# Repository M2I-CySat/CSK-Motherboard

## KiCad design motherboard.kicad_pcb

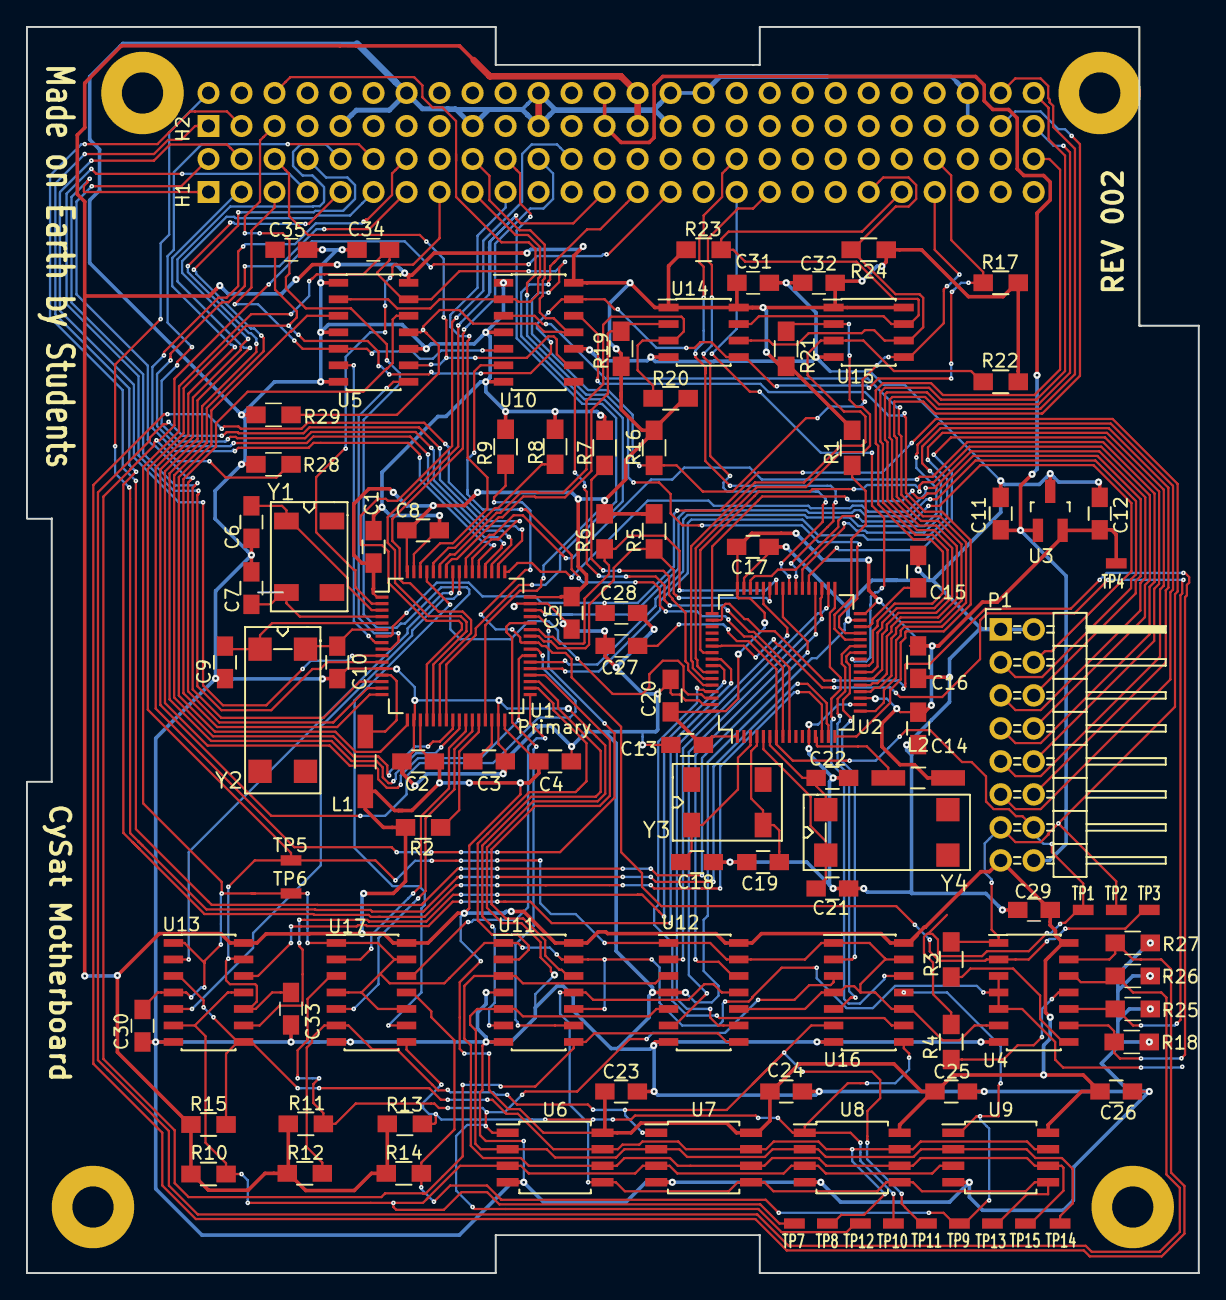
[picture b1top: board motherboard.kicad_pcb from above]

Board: 2 copper layers, 90.2 x 95.9 mm, 106 parts (1 on the bottom side), 123 nets.

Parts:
C1, C11, C12, C13, C27, C28: 1uF; C_0805_HandSoldering
C2, C4, C5, C8, C14, C16, C17, C20, C23, C24, C25, C26, C29, C30, C31, C32, C33, C34, C35: 0.1uF; C_0805_HandSoldering
C3, C15: 4.7uF; C_0805_HandSoldering
C6, C7, C18, C19: 4.3pF; C_0805_HandSoldering
C9, C10, C21, C22: 20pF; C_0805_HandSoldering
H1, H2: CONN_02X26; CSK_Header
L1, L2: BEAD; Choke_SMD_1206_Handsoldering
LOGO: LOGO
P1: CONN_02X08; Pin_Header_Angled_2x08
R1, R2, R3, R4, R5, R6, R7, R8, R9, R10, R11, R12, R13, R14, R15, R16, R17, R18, R25, R26, R27, R28, R29: 100K; R_0805_HandSoldering
R19, R20, R21, R22, R23, R24: 4.7K; R_0805_HandSoldering
TP1, TP2, TP3, TP4, TP5, TP6, TP7, TP8, TP9, TP10, TP11, TP12, TP13, TP14, TP15: TP; TP_0603
U1, U2: STM32F411-LQFP64; LQFP-64_10x10mm_Pitch0.5mm
U3: AP7313; SOT-23_Handsoldering
U4: 74LS00; SOIC-14_3.9x8.7mm_Pitch1.27mm
U5, U10, U11, U12, U13, U16, U17: 74LS125; SOIC-14_3.9x8.7mm_Pitch1.27mm
U6, U7, U8, U9: FM25V20A-G; SOIJ-8_5.3x5.3mm_Pitch1.27mm
U14, U15: PCA9517A; SOIC-8_3.9x4.9mm_Pitch1.27mm
Y1, Y3: 32k; SOJ-4_5.5mm
Y2, Y4: 8M(16pF); SOJ-4_9.4mm

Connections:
+3V3: C1.2, C2.2, C4.2, C5.2, C8.2, C23.2, C24.2, C25.2, C26.2, C29.1, C31.1, C32.1, H2.27, H2.28, L1.2, P1.15, R1.2, R2.2, R5.2, R6.2, R10.1, R11.1, R12.1, R13.1, R14.1, R15.1, R16.2, R17.2, R19.2, R20.2, R21.2, R22.2, R23.1, R24.1, U1.1, U1.19, U1.32, U1.48, U1.64, U4.14, U5.14, U6.8, U7.8, U8.8, U9.8, U10.14, U11.14, U12.14, U13.14, U14.1, U14.8, U15.1, U15.8, U16.14, U17.14
+5V: C11.1, H2.25, H2.26, P1.16, U3.1
/BOOT0_P: R8.1, U1.60
/BOOT0_S: R7.1, U2.60
/BOOT1_P: R2.1, U1.28
/BOOT1_S: R1.1, U2.28
/GPIO0: H1.1, U1.14
/GPIO1: H1.2, U1.15
/GPIO2: H1.3, U1.45
/GPIO3: H1.4, U1.10
/GPIO4: H1.7, U1.11
/GPIO5: H1.8, U1.24
/GPIO6: H1.9, U1.25
/GPIO7: H1.10, U1.39
/GPIO8: H1.11, U1.40
/GPIO9: H1.12, U1.51
/GPIO10: H1.13, U1.52
/GPIO11: H1.14, U1.53
/GPIO12: H1.15, U1.2
/I2C2_SCL: H1.20, U1.29
/I2C2_SDA: H1.19, U1.62
/I2C3_SCL: H2.6, U2.29
/I2C3_SDA: H2.5, U2.62
/MEM_CS0: R14.2, TP9.1, U9.1, U16.11, U17.11
/MEM_CS0_P: U1.33, U17.12
/MEM_CS0_S: U2.33, U16.12
/MEM_CS1: R13.2, TP10.1, U8.1, U16.8, U17.8
/MEM_CS1_P: U1.61, U17.9
/MEM_CS1_S: U2.61, U16.9
/MEM_CS2: R12.2, TP11.1, U7.1, U16.6, U17.6
/MEM_CS2_P: U1.27, U17.5
/MEM_CS2_S: U2.27, U16.5
/MEM_CS3: R11.2, TP12.1, U6.1, U16.3, U17.3
/MEM_CS3_P: U1.26, U17.2
/MEM_CS3_S: U2.26, U16.2
/MEM_MISO: TP14.1, U6.2, U7.2, U8.2, U9.2, U11.5, U12.5
/MEM_MISO_P: U1.35, U11.6
/MEM_MISO_S: U2.35, U12.6
/MEM_MOSI: TP13.1, U6.5, U7.5, U8.5, U9.5, U11.11, U12.11
/MEM_MOSI_P: U1.36, U11.12
/MEM_MOSI_S: U2.36, U12.12
/MEM_NHOLD: R15.2, TP8.1, U6.7, U7.7, U8.7, U9.7, U13.3, U13.8
/MEM_NHOLD_P: U1.57, U13.2
/MEM_NHOLD_S: U2.57, U13.9
/MEM_NWP: R10.2, TP7.1, U6.3, U7.3, U8.3, U9.3, U13.6, U13.11
/MEM_NWP_P: U1.56, U13.5
/MEM_NWP_S: U2.56, U13.12
/MEM_SCK: TP15.1, U6.6, U7.6, U8.6, U9.6, U11.3, U12.3
/MEM_SCK_P: U1.34, U11.2
/MEM_SCK_S: U2.34, U12.2
/NBUFEN_PRI: C30.1, C34.1, H1.45, R16.1, TP6.1, U4.3, U4.4, U4.5, U5.13, U11.1, U11.10, U11.13, U13.1, U13.4, U15.5, U17.1, U17.4, U17.10, U17.13
/NBUFEN_SEC: C33.1, C35.1, H1.46, R17.1, TP5.1, U4.6, U10.13, U12.1, U12.10, U12.13, U13.10, U13.13, U14.5, U16.1, U16.4, U16.10, U16.13
/NRST_P: C27.2, P1.13, R3.2, TP2.1, U1.7, U4.1
/NRST_S: C28.2, P1.14, R4.2, TP1.1, U2.7
/NYIELD_P: R9.1, TP3.1, U1.41, U4.2
/PRX_STX: R6.1, U1.43, U2.42
/PTX_SRX: R5.1, U1.42, U2.43
/RADIO_RR: H1.6, U5.9, U10.9
/RADIO_RR_P: U1.9, U5.8
/RADIO_RR_S: U2.9, U10.8
/RADIO_RX: H1.17, U5.2, U10.2
/RADIO_RX_P: U1.17, U5.3
/RADIO_RX_S: U2.17, U10.3
/RADIO_TR: H1.5, U5.5, U10.5
/RADIO_TR_P: U1.8, U5.6
/RADIO_TR_S: U2.8, U10.6
/RADIO_TX: H1.18, R29.2, U5.11, U10.11
/RADIO_TX_P: U1.16, U5.12
/RADIO_TX_S: U2.16, U10.12
/RST1_P: R18.1, U2.50, U4.9
/RST1_S: R26.1, U1.50, U4.12
/RST2_P: R25.1, U2.54, U4.10
/RST2_S: R27.1, U1.54, U4.13
/SGPIO0: H2.1, U2.14
/SGPIO1: H2.2, U2.15
/SGPIO2: H2.3, U2.41
/SGPIO6: H1.52, U2.24
/SGPIO7: H1.33, U2.25
/SGPIO8: H1.34, U2.39
/SGPIO9: H1.35, U2.40
/SPI2_MISO: H2.51, U2.22
/SPI2_MOSI: H2.52, U2.23
/SPI2_NSS: H2.49, U2.20
/SPI2_SCK: H2.50, U2.21
/SWO_P: P1.7, U1.55
/SWO_S: P1.8, U2.55
/SYS_RESET: H1.29, R28.2, U11.8, U12.8
/SYS_RESET_P: U1.44, U11.9
/SYS_RESET_S: U2.44, U12.9
/SYS_SCL: H1.43, R23.2, U14.7, U15.7
/SYS_SCL_P: R19.1, U1.58, U14.2
/SYS_SCL_S: R21.1, U2.58, U15.2
/SYS_SDA: H1.41, R24.2, U14.6, U15.6
/SYS_SDA_P: R20.1, U1.59, U14.3
/SYS_SDA_S: R22.1, U2.59, U15.3
/SYS_SPI_MISO: H1.22, U1.22
/SYS_SPI_MOSI: H1.27, U1.23
/SYS_SPI_NSS: H1.24, U1.20
/SYS_SPI_SCK: H1.25, U1.21
/TCK_P: P1.5, U1.49
/TCK_S: P1.6, U2.49
/TMS_P: P1.3, U1.46
/TMS_S: P1.4, U2.46
/UART2_RX: P1.11, U1.38
/UART2_TX: P1.9, U1.37
/UART3_RX: P1.12, U2.38
/UART3_TX: P1.10, U2.37
/VDD_S: C12.1, C13.2, C14.2, C16.2, C17.2, C20.2, L2.2, TP4.1, U2.1, U2.19, U2.32, U2.48, U2.64, U3.2
GND: C1.1, C2.1, C3.1, C4.1, C5.1, C6.1, C7.1, C8.1, C9.1, C10.1, C11.2, C12.2, C13.1, C14.1, C15.1, C16.1, C17.1, C18.1, C19.1, C20.1, C21.1, C22.1, C23.1, C24.1, C25.1, C26.1, C27.1, C28.1, C29.2, C30.2, C31.2, C32.2, C33.2, C34.2, C35.2, H2.9, H2.14, H2.17, H2.21, H2.22, H2.29, H2.30, H2.32, H2.47, H2.48, P1.1, P1.2, R7.2, R8.2, R9.2, R18.2, R25.2, R26.2, R27.2, R28.1, R29.1, U1.12, U1.18, U1.31, U1.47, U1.63, U2.12, U2.18, U2.31, U2.47, U2.63, U3.3, U4.7, U5.1, U5.4, U5.7, U5.10, U6.4, U7.4, U8.4, U9.4, U10.1, U10.4, U10.7, U10.10, U11.4, U11.7, U12.4, U12.7, U13.7, U14.4, U15.4, U16.7, U17.7
unnamed: C3.2, U1.30
unnamed: C6.2, U1.3, Y1.1
unnamed: C7.2, U1.4, Y1.2
unnamed: C9.2, U1.5, Y2.1
unnamed: C10.2, U1.6, Y2.2
unnamed: C15.2, U2.30
unnamed: C18.2, U2.3, Y3.1
unnamed: C19.2, U2.4, Y3.2
unnamed: C21.2, U2.5, Y4.1
unnamed: C22.2, U2.6, Y4.2
unnamed: L1.1, U1.13
unnamed: L2.1, U2.13
unnamed: R3.1, U4.8
unnamed: R4.1, U4.11

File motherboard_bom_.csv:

Component,Description,Part,References,Value,Footprint,Quantity Per PCB,Datasheet,Thermal Coefficient,Digikey Part Number,Mouser Part Number
1,Unpolarized capacitor,C,C2 C4 C5 C8 C14 C16 C17 C20 C23 C24 C25 C26 C29 C30 C31 C32 C33 C34 C35,0.1uF,C_0805_HandSoldering,19,,,478-1395-1-ND,
2,Unpolarized capacitor,C,C1 C11 C12 C13 C27 C28,1uF,C_0805_HandSoldering,6,,X5R,399-1284-1-ND,
3,Unpolarized capacitor,C,C9 C10 C21 C22,20pF,C_0805_HandSoldering,4,,,1276-1829-1-ND,
4,Unpolarized capacitor,C,C6 C7 C18 C19,4.3pF,C_0805_HandSoldering,4,,,478-10404-1-ND ,
5,Unpolarized capacitor,C,C3 C15,4.7uF,C_0805_HandSoldering,2,,,490-5422-1-ND,
6,,CONN_02X26,H1 H2,CONN_02X26,CSK_Header,2,,,SAM1183-26-ND,
7,,INDUCTOR_SMALL,L1 L2,BEAD,Choke_SMD_1206_Handsoldering,2,,,535-11657-1-ND,
8,,CONN_02X08,P1,CONN_02X08,Pin_Header_Angled_2x08,1,,,609-3337-ND,
9,Resistor,R,R1 R2 R3 R4 R5 R6 R7 R8 R9 R10 R11 R12 R13 R14 R15 R16 R17 R18 R25 R26 R27 R28 R29,100K,R_0805_HandSoldering,23,,,311-100KCRCT-ND ,
10,Resistor,R,R19 R20 R21 R22 R23 R24,4.7K,R_0805_HandSoldering,6,,,311-4.70KCRCT-ND,
11,Quad nand2,74LS00,U4,74LS00,SOIC-14_3.9x8.7mm_Pitch1.27mm,1,,,296-14873-1-ND,
12,Quad buffer 3 State out,74LS125,U5 U10 U11 U12 U13 U16 U17,74LS125,SOIC-14_3.9x8.7mm_Pitch1.27mm,7,,,296-3642-1-ND,
13,"150mA Low Dropout Voltage Regulator, Fixed Output 1.2V, SOT-23",AP7313,U3,AP7313,SOT-23_Handsoldering,1,,,AP7313-18SAG-7DICT-ND ,
14,FRAM SPI 2MBit,FM25V20A-G,U6 U7 U8 U9,FM25V20A-G,SOIC-8_3.9x4.9mm_Pitch1.27mm,4,,,FM25V20A-G-ND,
15,I2C Buffer With Enable,PCA9517A,U14 U15,PCA9517A,SOIC-8_3.9x4.9mm_Pitch1.27mm,2,,,296-23734-1-ND,
16,ARM Cortex M4 Microcontroller,STM32F411-LQFP64,U1 U2,STM32F411-LQFP64,LQFP-64_10x10mm_Pitch0.5mm,2,,,,511-STM32F411RET6 
17,Two pin crystal,Crystal,Y1 Y3,32k,SOJ-4_5.5mm,2,,,535-10242-1-ND ,
18,Two pin crystal,Crystal,Y2 Y4,8M(16pF),SOJ-4_9.4mm,2,,,XC2041-1-ND ,
,,,,,,,,,,
,,,,,,,,,,
,,,,,,,,,,
,,,,,,,,,,
,,,,,,,,,,
Component Groups:,18,,,,,,,,,
Component Count:,90,,,,,,,,,
Fitted Components:,90,,,,,,,,,
Number of PCBs:,1,,,,,,,,,
Total components:,90,,,,,,,,,
Schematic Version:,,,,,,,,,,
Schematic Date:,,,,,,,,,,
BoM Date:,Mon 16 Oct 2017 12:35:08 PM CDT,,,,,,,,,
Schematic Source:,/home/nate/Documents/CySat-Motherboard/motherboard.sch,,,,,,,,,
KiCad Version:,Eeschema 4.0.7-e2-6376~58~ubuntu16.04.1,,,,,,,,,

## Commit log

2016-01-31 Work done on buffers and MCU placement
2016-02-23 Did some stuff
2016-02-23 Added rescue
2016-02-23 Began adding memory
2016-02-24 Put FRAM on motherboard
2016-03-13 Work on schematic
2016-03-13 Very nearly done
2016-03-14 Shit's done, yo
    The schematic, that is.
2016-03-14 Created PDF
2016-11-05 Added pinout PDF
2016-11-05 Began adding real connectors to schematic
2016-11-29 Changed pinout
2016-11-29 Added radio interrupt lines
2016-11-30 Associated symbols with footprints
    Created a few modules as needed
2016-11-30 Design rules
2016-12-03 Started BOM
2016-12-03 Finished board outline and connector placement
    Beginning to assign GPIOs and layout components
2016-12-04 Schematic passes DRC
2016-12-04 Progress in laying out components
2016-12-05 Placed all components
2017-02-03 Routed P1 High-speed signals
    - Main UART
    - Main I2C
    - Mem SPI
2017-02-03 Much more routing completed.
2017-02-05 More routing
2017-02-11 Added IDF export files
2017-04-07 Made sure PDF is absolutely up-to-date
2017-04-08 Added boards to datasheets
2017-04-08 Added notes
2017-04-08 Added STM32 datasheet
2017-04-22 Implemented recommendations from design meeting.
2017-04-22 Began placing new components
2017-04-26 All components placed
    Most signals routed
2017-04-26 Plotted PDF and gerbers
2017-09-15 Replaced backwards CSK headers
    Connectors were mirrored, so that sucks. Connectors replaced,
    but all traces to headers need to be re-routed.
2017-10-08 Primary GPIO routed
2017-10-09 Added silkscreen revision tag
2017-10-16 Add a preliminary bill of materials
2017-11-01 Started Digi-Key part numbers
2017-11-03 Finished DigiKey part numbers
2017-11-04 Removed fake BoM
2018-03-29 Fixed wireplacement, moved values to facilitate eaiser assembly, Added text and logo
2018-03-30 Removed tumor
2018-03-30 Add issues with revision one list
2018-04-07 Added footprint directory
2018-04-07 Added footprint directory part deux
2018-04-07 Adding ground plane
2018-04-07 Added ground plane and fixed footprints
2018-04-07 added logo to footprints
2018-04-07 Fixed pull-ups on NRST lines
    Also fixed naming of RSTn_m lines.
2018-04-08 Partial rerouting following resistor movement
    Moving the fixed Pull-Up resistors to NAND output made a bunch of
    traces have to move.
    Not yet complete.
2018-04-08 Nuked gerber
2018-04-08 Finished Rev2 reworks
    - Addressed documented issues
    - Some SGPIO is not connected (see schematic for details)
    - Created direct return paths for MEM_SPI
2018-04-09 Changed revision number on board
2018-04-09 Ran DRC, checking for changes
2018-05-21 Added pinout PDF
    It is still accurate.
2018-06-15 Updated bom
2018-07-28 Fixed pc104 conflicts
2018-07-28 added zip
2018-07-30 Fixed gerber files
